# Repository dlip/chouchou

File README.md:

# Chouchou Keyboard/Fight Pad

Chouchou (Japanese for butterfly) is a minimalist unibody keyboard designed to be used with the [Taipo](https://inkeys.wiki/en/keymaps/taipo) layout, but it also can be used as a pretty nice fighting gamepad.

It uses a cheap RP2040-Zero MCU and requires no diodes since the 20 edge pinouts it provides is the exact number of keys Taipo requires. It was created with [Ergogen](https://github.com/ergogen/ergogen) and [KiCad](https://www.kicad.org). I designed it for my largish hands so if you have smaller hands its probably not going to be comfortable. I might make a more compact version in the future if people request it.

## Fight Pad / Pin Layout

## Build Your Own

### Board

#### Parts

- Send the [Gerber](kicad/gerber_to_order) file to the PCB manufacturer of your choice
- 1 x RP2040-Zero
- 20 x low profile choc switches and keycaps. Since you're going to be doing a lot of combos, I recommend lighter switches. I use 25g light blue, but 35g pro red is not bad either. You can use 1.5U keycaps for the thumbs, the socket has been rotated 90 degrees to accomodate.
- (optional) 20 x kailh hotswap sockets
- (optional) RP2040-Zero headers

#### Firmware

- [QMK](https://github.com/dlip/qmk_firmware/tree/chouchou/keyboards/chouchou)
  - Taipo Keyboard
  - PC Gamepad
  - Qwerty/WASD Layout
- [KMK](firmware/kmk)
  - Taipo Keyboard
  - Python based with hot reloading so good if you tinker a lot with your layout
- [GP2040-CE](firmware/gp2040-ce)
  - PC or console gamepad
  - Note: PS5 requires an adapter like the [Wingman FGC](https://shop.brookaccessory.com/en/products/wingman-fgc)

#### Instructions

- Solder the RP2040-Zero to the board either directly or using the headers you purchased
- Build and flash the firmware
- You can test the keyboard at this point by connecting the hotswap pads with some metal tweezers before continuing
- Solder the kalih hotswap sockets if purchased or solder the switches directly the board otherwise
- Insert the switches into the hotswap sockets if necessary
- Add your keycaps 

### Case

Issue: The case gets blocked by one of the screw mounts when using hotswap sockets, its easy enough to cut the side a bit with a knife though. 

#### Parts

The screws/nuts are optional, its a pretty tight fit so you might not need them.

- 3D print the [case.stl](case/case.stl) file
- (optional)  8 x Knurled Insert Nuts (M2 x 3mm Length x 3.2mm OD) [example](https://www.amazon.com/dp/B07LBQFNQD)
- (optional) 8 x M2 3mm flat screws [example](https://www.amazon.com/gp/product/B01FTI8TM8/) 

#### Instructions

- Use a soldering iron to melt the insert nuts into the holes in the case
- Screw the board to the case

### Attribution

Butterfly image by [Freepik](https://www.freepik.com/free-vector/hand-drawn-butterfly-outline-pack_15636314.htm#query=butterfly&position=29&from_view=keyword&track=sph)

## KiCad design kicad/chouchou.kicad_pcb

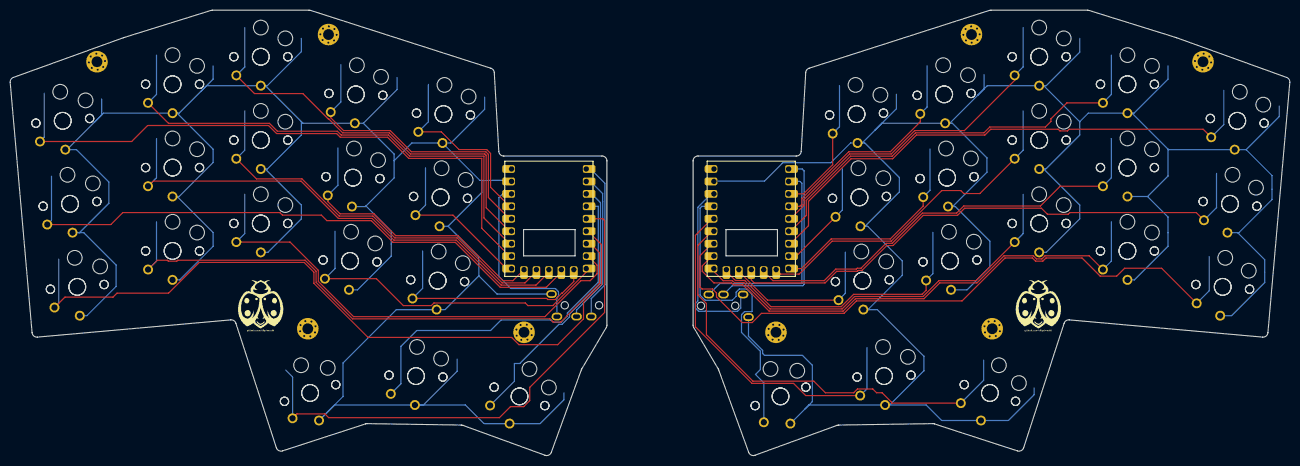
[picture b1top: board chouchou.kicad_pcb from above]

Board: 2 copper layers, 261.0 x 90.8 mm, 84 parts (0 on the bottom side), 44 nets.

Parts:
RP2040Zero1, RP2040Zero2: RP2040-Zero
S1, S2, S3, S4, S5, S6, S7, S8, S9, S10, S11, S12, S13, S14, S15, S16, S17, S18, S19, S20, S21, S22, S23, S24, S25, S26, S27, S28, S29, S30, S31, S32, S33, S34, S35, S36, S37, S38, S39, S40, S41, S42, S43, S44, S45, S46, S47, S48, S49, S50, S51, S52, S53, S54, S55, S56, S57, S58, S59, S60, S61, S62, S63, S64, S65, S66, S67, S68, S69, S70, S71, S72: PG1350
TRRS1, TRRS2: TRRS-PJ-320A-dual
_1, _2, _3, _4, _5, _6, _7, _8: MountingHole_2.2mm_M2_Pad_Via

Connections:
GND: RP2040Zero1.20, S1.2, S2.2, S3.2, S4.2, S5.2, S6.2, S7.2, S8.2, S9.2, S10.2, S11.2, S12.2, S13.2, S14.2, S15.2, S16.2, S17.2, S18.2, S19.2, S20.2, S21.2, S22.2, S23.2, S24.2, S25.2, S26.2, S27.2, S28.2, S29.2, S30.2, S31.2, S32.2, S33.2, S34.2, S35.2, S36.2, TRRS1.1
P3V3: RP2040Zero1.21, TRRS1.2
RX: RP2040Zero1.2, TRRS1.3
TX: RP2040Zero1.1, TRRS1.4
matrix_index_bottom: RP2040Zero1.9, S10.1, S28.1
matrix_index_middle: RP2040Zero1.14, S11.1, S29.1
matrix_index_top: RP2040Zero1.22, S12.1, S30.1
matrix_middle_bottom: RP2040Zero1.8, S7.1, S25.1
matrix_middle_middle: RP2040Zero1.13, S8.1, S26.1
matrix_middle_top: RP2040Zero1.18, S9.1, S27.1
matrix_outer_bottom: RP2040Zero1.10, S13.1, S31.1
matrix_outer_middle: RP2040Zero1.15, S14.1, S32.1
matrix_outer_top: RP2040Zero1.23, S15.1, S33.1
matrix_pinky_bottom: RP2040Zero1.6, S1.1, S19.1
matrix_pinky_middle: RP2040Zero1.11, S2.1, S20.1
matrix_pinky_top: RP2040Zero1.16, S3.1, S21.1
matrix_ring_bottom: RP2040Zero1.7, S4.1, S22.1
matrix_ring_middle: RP2040Zero1.12, S5.1, S23.1
matrix_ring_top: RP2040Zero1.17, S6.1, S24.1
mirror_matrix_index_bottom: RP2040Zero2.14, S46.1, S64.1
mirror_matrix_index_middle: RP2040Zero2.9, S47.1, S65.1
mirror_matrix_index_top: RP2040Zero2.4, S48.1, S66.1
mirror_matrix_middle_bottom: RP2040Zero2.15, S43.1, S61.1
mirror_matrix_middle_middle: RP2040Zero2.10, S44.1, S62.1
mirror_matrix_middle_top: RP2040Zero2.5, S45.1, S63.1
mirror_matrix_outer_bottom: RP2040Zero2.13, S49.1, S67.1
mirror_matrix_outer_middle: RP2040Zero2.8, S50.1, S68.1
mirror_matrix_outer_top: RP2040Zero2.3, S51.1, S69.1
mirror_matrix_pinky_bottom: RP2040Zero2.17, S37.1, S55.1
mirror_matrix_pinky_middle: RP2040Zero2.12, S38.1, S56.1
mirror_matrix_pinky_top: RP2040Zero2.7, S39.1, S57.1
mirror_matrix_ring_bottom: RP2040Zero2.16, S40.1, S58.1
mirror_matrix_ring_middle: RP2040Zero2.11, S41.1, S59.1
mirror_matrix_ring_top: RP2040Zero2.6, S42.1, S60.1
mirror_thumbs_inner_cluster: RP2040Zero2.18, S52.1, S70.1
mirror_thumbs_middle_cluster: RP2040Zero2.22, S53.1, S71.1
mirror_thumbs_outer_cluster: RP2040Zero2.23, S54.1, S72.1
rGND: RP2040Zero2.20, S37.2, S38.2, S39.2, S40.2, S41.2, S42.2, S43.2, S44.2, S45.2, S46.2, S47.2, S48.2, S49.2, S50.2, S51.2, S52.2, S53.2, S54.2, S55.2, S56.2, S57.2, S58.2, S59.2, S60.2, S61.2, S62.2, S63.2, S64.2, S65.2, S66.2, S67.2, S68.2, S69.2, S70.2, S71.2, S72.2, TRRS2.1
rP3V3: RP2040Zero2.21, TRRS2.2
rRX: RP2040Zero2.2, TRRS2.4
rTX: RP2040Zero2.1, TRRS2.3
thumbs_inner_cluster: RP2040Zero1.5, S16.1, S34.1
thumbs_middle_cluster: RP2040Zero1.4, S17.1, S35.1
thumbs_outer_cluster: RP2040Zero1.3, S18.1, S36.1

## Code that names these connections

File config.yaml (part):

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        height: trrs_y
    holePinkyTop:
      anchor:
        ref: [matrix_pinky_top]
        shift: [0.4px,0.6py]
    holeIndexTop:
      anchor:
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      operation: stack
      fillet: 1
      points:
        - ref: matrix_pinky_top
          shift: [-0.5px,0.5py]
        - ref: matrix_ring_top
          shift: [-0.5px,0.5py]
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          shift: [-0.5px,-0.5py]
        - ref: thumbs_inner_cluster
          shift: [-0.5px,1py]
        - ref: matrix_pinky_bottom
          shift: [-0.5px,-0.5py]
  boardRight:
    - what: polygon
      operation: stack
      fillet: 1
      points:
        - ref: mirror_matrix_pinky_top
          shift: [-0.5px,0.5py]
        - ref: mirror_matrix_ring_top
          shift: [-0.5px,0.5py]
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          shift: [-0.5px,-0.5py]
        - ref: mirror_thumbs_inner_cluster
          shift: [-0.5px,1py]
        - ref: mirror_matrix_pinky_bottom
          shift: [-0.5px,-0.5py]
  board:
    - boardLeft
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          GP28: matrix_index_top
          GP27: matrix_middle_top
          GP26: matrix_ring_top
          GP15: matrix_pinky_top
          GP14: matrix_outer_middle
          GP13: matrix_index_middle
          GP12: matrix_middle_middle
          GP11: matrix_ring_middle
          GP10: matrix_pinky_middle
          GP9:  matrix_outer_bottom
          GP8:  matrix_index_bottom
          GP7:  matrix_middle_bottom
          GP6:  matrix_ring_bottom
          GP5:  matrix_pinky_bottom
          GP4:  thumbs_inner_cluster
          GP3:  thumbs_middle_cluster
          GP2:  thumbs_outer_cluster
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          GP29: mirror_thumbs_outer_cluster
          GP28: mirror_thumbs_middle_cluster
          GP27: mirror_thumbs_inner_cluster
          GP26: mirror_matrix_pinky_bottom
          GP15: mirror_matrix_ring_bottom
          GP14: mirror_matrix_middle_bottom
          GP13: mirror_matrix_index_bottom
          GP12: mirror_matrix_outer_bottom
          GP11: mirror_matrix_pinky_middle
          GP10: mirror_matrix_ring_middle
          GP9:  mirror_matrix_middle_middle
          GP8:  mirror_matrix_index_middle
          GP7:  mirror_matrix_outer_middle
          GP6:  mirror_matrix_pinky_top
          GP5:  mirror_matrix_ring_top
          GP4:  mirror_matrix_middle_top
          GP3:  mirror_matrix_index_top
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
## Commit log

2023-07-17 Add ergogen files
2023-07-17 Add kicad project
2023-07-17 add wiring
2023-07-18 Update design
2023-07-18 Add build scripts
2023-07-18 Add case
2023-07-18 Add images
2023-07-19 remove extra point
2023-07-19 move screws
2023-07-19 update case holes
2023-07-19 Add ordered files
2023-07-19 use gerber to order plugin
2023-07-20 Increase case thickness
2023-07-27 Add initial kmk setup
2023-07-28 Improve kmk
2023-07-28 Try using key names to reduce combos
2023-07-29 Add case image
2023-07-29 Add board image
2023-07-29 Add switch comment
2023-07-29 Add thumbswitch note
2023-07-30 update issues
2023-08-01 Add gp2040 config
2023-08-01 Update title
2023-08-01 Add gp2040 instructions
2023-08-01 Add layout
2023-08-01 Update layout
2023-08-01 fix link
2023-08-02 Fix header
2023-08-09 start split version
2023-08-09 update pins
2023-08-09 fix nets
2023-08-10 move to reversable design
2023-08-10 Revert "move to reversable design"
    This reverts commit 7f9bf7a120195808f756752224842760519c8f40.
2023-08-10 wire dual board
2023-08-10 try flipped
2023-08-10 add hole points
2023-08-10 fix holes
2023-08-10 remove some points
2023-08-10 add connections
2023-08-11 add trrs
2023-08-11 fix net
2023-08-11 extra stagger
2023-08-12 compact design
2023-08-13 start custom kmk combos
2023-08-13 basic handling
2023-08-13 fix reference
2023-08-13 handle keys
2023-08-13 add mods
2023-08-13 fix modules
2023-08-13 add tap timeout
2023-08-13 fix module order
2023-08-13 Add kmk info
2023-08-13 disable debug
2023-08-16 add some stagger
2023-08-16 try mini
2023-08-16 shrink more
2023-08-17 add top gap
2023-08-17 add steno layout
2023-08-17 add padding
2023-08-25 add pcb
2023-08-25 fiddle
2023-08-26 Update holes
2023-08-26 Connect pcb
2023-08-26 Cleanup tracks
2023-08-26 add extra thumb
2023-08-27 tweaking
2023-08-27 Add traces
2023-08-27 use full duplex serial
2023-08-27 Full duplex
2023-08-27 ignore warnings
2023-08-27 add logo
2023-09-16 Add license
2024-07-21 Update gp2040
